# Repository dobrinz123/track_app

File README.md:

# Circuit Timer

An **advisory, recreational** GNSS lap-timing app for the Transilvania Motor Ring (Cerghid, Mureș County, Romania) — not an official timing system, and no substitute for organizer or FIM/FIA timing. It's a React Native / Expo app (iOS-first, Android supported) backed by a pure TypeScript timing/geometry core.

See `docs/decisions/ADR-0001-stack.md` for the stack decision, `docs/decisions/ADR-0003-ios-primary-target.md` for why iOS is the primary target, and `docs/architecture/contracts.md` for the binding module contracts.

## Quickstart (Windows + iPhone, free sideload path)

Expo Go is retired for this app's SDK — there's no more QR-code dev loop. Both
development and on-track use now go through a sideloaded standalone build. See
[`docs/ios-no-mac-workflow.md`](docs/ios-no-mac-workflow.md) for the full,
beginner-proof guide: the GitHub Actions workflow that builds unsigned `.ipa`
artifacts, and installing/re-signing them on Windows with Sideloadly and a free
Apple ID (no paid Apple Developer account required).

```
npm install
```

Then follow [`docs/ios-no-mac-workflow.md`](docs/ios-no-mac-workflow.md) §b onward to
build via CI, sideload to your iPhone, and (§e) run the dev-client build against
`npx expo start` from `apps/mobile` for fast iteration.

## Monorepo layout

npm workspaces (`packages/*`, `apps/*`):

```
packages/core/    @circuit/core — pure TypeScript domain package (geometry, timing,
                  calibration, session-state contracts). Zero React/React
                  Native/Expo imports, enforced by an ESLint no-restricted-imports
                  rule. Vitest + fast-check for unit/property tests, Zod for schema
                  validation.
apps/mobile/      mobile — Expo (TypeScript) app. Imports @circuit/core via
                  the workspace; Metro is configured for monorepo resolution.
```

## Prerequisites

- Node.js 24.x and npm 11.x.
- No Android SDK / Xcode / Flutter required for typecheck, test, lint, or the
  Metro export steps below. Native builds (APK/IPA) additionally require Android
  Studio / Xcode (out of scope on this Windows build machine) or
  [EAS Build](https://docs.expo.dev/build/introduction/), which runs in the cloud
  and needs neither — see `docs/ios-no-mac-workflow.md` for the iOS path.

## Install

```
npm install
```

Installs and links all workspaces from the repo root (do not `npm install` inside
individual packages).

## Verification commands

From the repo root:

```
npm run typecheck   # tsc --noEmit across all workspaces
npm test             # vitest run in packages/core
npm run lint          # eslint . (flat config, applied to both workspaces)
npm run format         # prettier --write .
```

To verify the mobile app bundles correctly with Metro (no Android SDK / Xcode needed —
both platforms are machine-verifiable gates per `docs/decisions/ADR-0003-ios-primary-target.md` §5):

```
cd apps/mobile
npx expo export --platform ios --output-dir dist-export
npx expo export --platform android --output-dir dist-export
```

To run the app itself on an iPhone: a sideloaded dev-client build (see Quickstart above
and `docs/ios-no-mac-workflow.md`), or `npm run ios` / `npm run android` / `npm run web`
from `apps/mobile` with the relevant SDK/simulator installed.

## Docs index

- [`docs/ios-no-mac-workflow.md`](docs/ios-no-mac-workflow.md) — canonical Windows-host,
  iPhone-device workflow: free unsigned-`.ipa` CI builds + Sideloadly (dev-client and
  release, no paid account), offline on-track operation, troubleshooting.
- [`docs/verification/real-track-validation-checklist.md`](docs/verification/real-track-validation-checklist.md) —
  printable physical validation protocol at Transilvania Motor Ring.
- [`docs/verification/baseline.md`](docs/verification/baseline.md) — repository state at project start.
- [`docs/architecture/contracts.md`](docs/architecture/contracts.md) — binding module contracts (canonical interfaces).
- [`docs/architecture/current-state.md`](docs/architecture/current-state.md) — living summary of the target architecture.
- [`docs/implementation-plan.md`](docs/implementation-plan.md) — work-package breakdown and verification strategy.
- [`docs/research/transilvania-motor-ring.md`](docs/research/transilvania-motor-ring.md) — circuit research packet
  (location, length, OSM geometry addendum, known gaps).
- [`docs/decisions/ADR-0001-stack.md`](docs/decisions/ADR-0001-stack.md) — mobile stack: React Native (Expo) + TypeScript monorepo.
- [`docs/decisions/ADR-0002-circuit-geometry-source.md`](docs/decisions/ADR-0002-circuit-geometry-source.md) — circuit geometry
  provenance (OSM-derived centerline, app-defined gates) and license attribution.
- [`docs/decisions/ADR-0003-ios-primary-target.md`](docs/decisions/ADR-0003-ios-primary-target.md) — iOS as the primary
  target platform: Location configuration, Info.plist, monotonic timing, thermal/battery, verification gates.
- [`docs/decisions/ADR-0004-no-mac-ios-workflow.md`](docs/decisions/ADR-0004-no-mac-ios-workflow.md) — iOS without a Mac:
  original Expo Go development + EAS cloud builds decision; dev-loop portion superseded by ADR-0005.
- [`docs/decisions/ADR-0005-free-install-path.md`](docs/decisions/ADR-0005-free-install-path.md) — free iOS install
  path: GitHub Actions unsigned `.ipa` builds + Sideloadly (free Apple ID), replacing the retired Expo Go dev loop.
- [`docs/algorithms/calibration.md`](docs/algorithms/calibration.md) — the Learn-lap calibration engine: quality
  thresholds, coverage bins, direction detection, bounded bias estimation, acceptance criteria, confidence blend.
- [`docs/algorithms/timing-and-crossings.md`](docs/algorithms/timing-and-crossings.md) — directed-gate crossing
  semantics, rearm/debounce, lap/sector validity rules and invalid-reason codes, monotonic-time rules.
- [`docs/algorithms/live-delta.md`](docs/algorithms/live-delta.md) — reference-lap resampling, PB replacement rules,
  live delta computation, EMA smoothing, confidence/staleness handling, sign convention.
- [`docs/persistence-model.md`](docs/persistence-model.md) — SQL table schema (v1/v2), migration approach, checkpoint
  cadence, ADR-0003 §3 recovery flow, `sessionId` convention, `deleteUserData` coverage, retention.
- [`docs/testing-and-replay.md`](docs/testing-and-replay.md) — test architecture (unit/property/contract/integration),
  the fixture catalog, how to run the suites, using `DevReplayScreen` on-device, determinism rules.
- [`docs/known-limitations.md`](docs/known-limitations.md) — an honest list of the app's real constraints and
  implementation gaps.
- [`docs/privacy.md`](docs/privacy.md) — data inventory, permission posture, deletion path, diagnostics content,
  the advisory-tool disclaimer.
- [`docs/adding-a-circuit.md`](docs/adding-a-circuit.md) — onboarding a future circuit: profile schema, provenance
  rules, the generator-script pattern, validation gates, `layoutVersion` discipline.

## License / attribution

Circuit centerline and pit-lane geometry are derived from OpenStreetMap (way `488429454` and way `488429716`),
© OpenStreetMap contributors, licensed under the **Open Database License (ODbL) 1.0**. Start/finish and sector
gates are **app-defined**, not official — see `docs/decisions/ADR-0002-circuit-geometry-source.md` for full
provenance and the attribution requirement.

## Known limitations

- Native binaries are not built or verified on this machine; only the Metro
  (JS bundle) export is machine-verifiable here, per `docs/decisions/ADR-0001-stack.md`.
  Native builds (APK/IPA) run via EAS Build in the cloud.
- Circuit geometry is community-derived (OpenStreetMap), and start/finish/sector gates
  are app-defined, not sourced from official circuit or FIM/FIA documentation — see
  `docs/decisions/ADR-0002-circuit-geometry-source.md`. Physical on-track validation
  (`docs/verification/real-track-validation-checklist.md`) is the reference check against
  this gap.

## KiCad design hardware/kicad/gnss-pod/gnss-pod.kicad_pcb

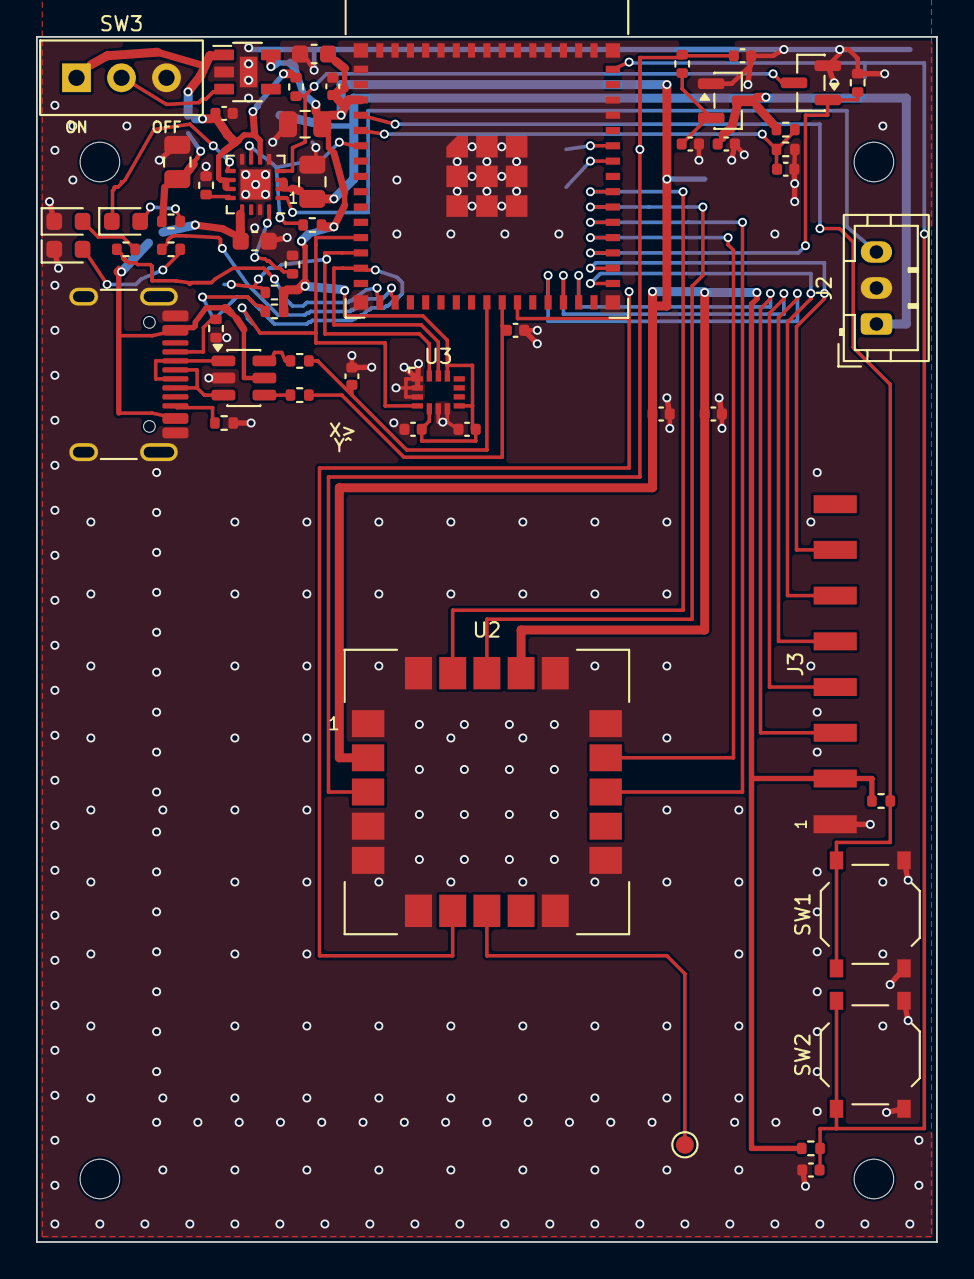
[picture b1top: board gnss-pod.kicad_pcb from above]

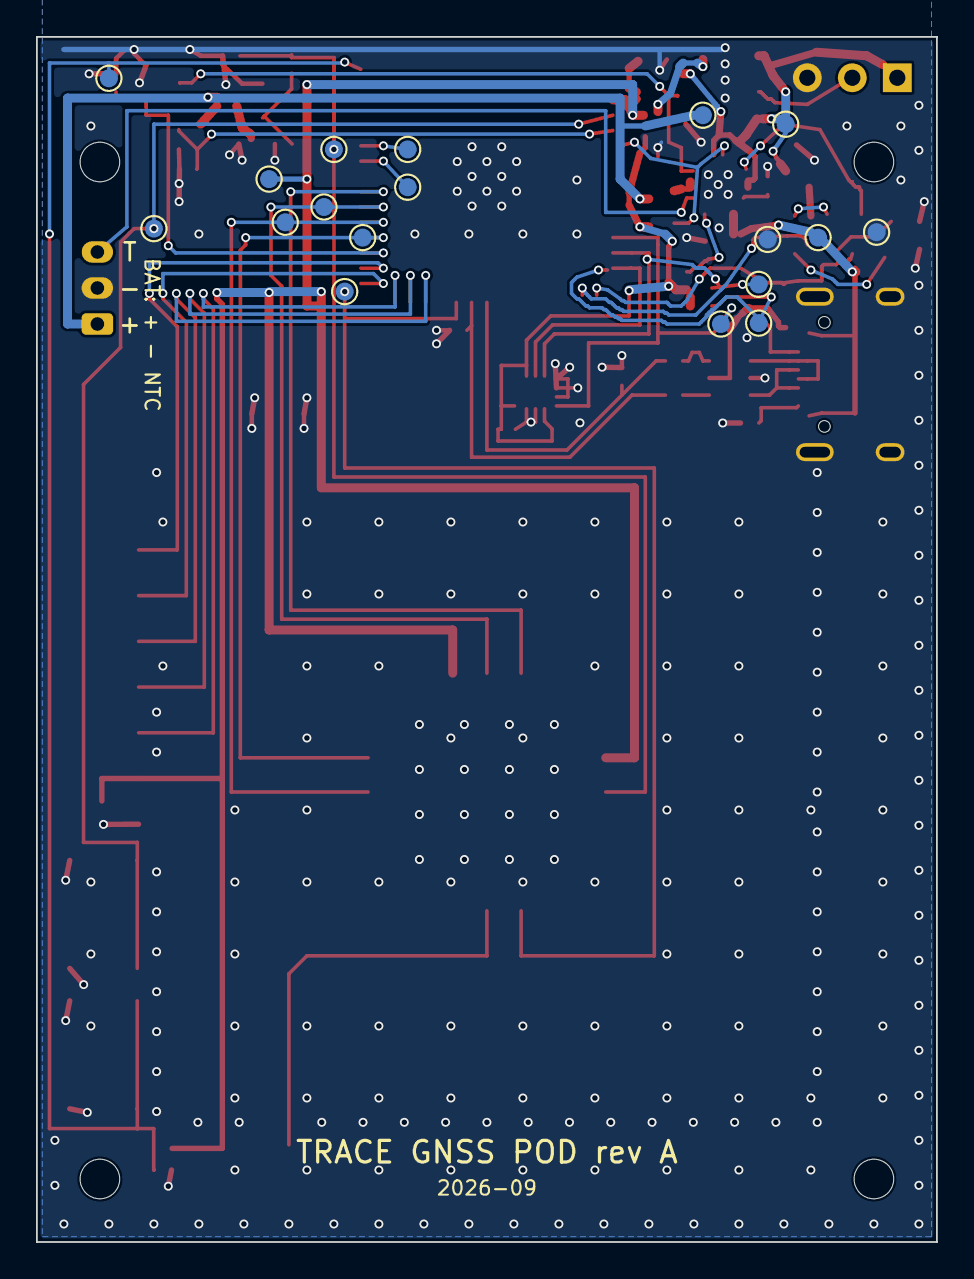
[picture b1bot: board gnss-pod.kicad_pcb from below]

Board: 2 copper layers, 50.0 x 67.0 mm, 77 parts (18 on the bottom side), 45 nets.

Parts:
C1: 1uF 50V X5R 0603; C_0603_1608Metric
C2, C3, C6: 22uF 25V X5R 0805; C_0805_2012Metric
C4, C8, C12, C13: 1uF 25V X5R 0402; C_0402_1005Metric
C5: 10uF 10V X5R 0603; C_0603_1608Metric
C7, C10, C11, C14, C15, C16: 100nF 16V X7R 0402; C_0402_1005Metric
C9: 4.7uF 10V X5R 0402; C_0402_1005Metric
C17, C18: DNP; C_0402_1005Metric
J1: TYPE-C-31-M-12; USB_C_Receptacle_HRO_TYPE-C-31-M-12
J2: B3B-PH-K-S(LF)(SN); JST_PH_B3B-PH-K_1x03_P2.00mm_Vertical
J3: DNP 1x8 spare pads; PadRow_1x08_P2.54mm_SMD
LED1: KT-0603Y yellow; LED_0603_1608Metric
LED2: KT-0603R red; LED_0603_1608Metric
LED3: KT-0603R red CHG; LED_0603_1608Metric
MH1, MH2, MH3, MH4: M2; MountingHole_2.2mm_M2
Q1: 2N7002; SOT-23
R1, R2: 5.1k 1%; R_0402_1005Metric
R3, R4: 22R; R_0402_1005Metric
R5, R6, R19: 10k 1%; R_0402_1005Metric
R7, R8: 4.7k 1%; R_0402_1005Metric
R9: 3.3k 1%; R_0402_1005Metric
R10, R11: 1.5k 1%; R_0402_1005Metric
R12, R18: 100k 1%; R_0402_1005Metric
R13, R14: 1M 1%; R_0402_1005Metric
R15, R16: 1k 1%; R_0402_1005Metric
R17: 0R; R_0402_1005Metric
SW1: TS-1187A-B-A-B BOOT; SW_Push_1P1T_XKB_TS-1187A
SW2: TS-1187A-B-A-B RESET; SW_Push_1P1T_XKB_TS-1187A
SW3: SS-12D00-G3 POWER; SW_Slide_SPDT_SOFNG_SS-12D00-G3
TP1, TP2, TP3, TP4, TP5, TP6, TP7, TP8, TP9, TP10, TP11, TP12, TP13, TP14, TP15, TP16, TP17, TP18, TP19: TP; TestPoint_Pad_D1.0mm
U1: ESP32-S3-MINI-1-N8; ESP32-S3-MINI-1
U2: SAM-M10Q-00B; u-blox_SAM-M10Q
U3: LSM6DSV16XTR; LGA-14_2.5x3mm_P0.5mm_LSM6DSV16X
U4: BQ24073RGTR; TI_RGT0016C_VQFN-16_3x3mm_P0.5mm_EP1.68mm
U5: TLV75733PDYDR; TI_DYD0005A_SOT-23-5_ThermalPad
U6: XC6206P332MR-G; SOT-23
U7: USBLC6-2SC6; SOT-23-6_USBLC6-2_FlowThrough

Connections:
3V3: C5.1, C6.1, C7.1, C9.1, C10.1, C14.1, C15.1, J3.2, R5.2, R6.2, R7.2, R8.2, R12.2, TP1.1, U1.3, U2.2, U2.17, U3.5, U3.8, U3.12, U5.5
BOOT: R6.1, SW1.1, TP17.1, U1.4
CC1: J1.A5, R1.1
CC2: J1.B5, R2.1
CHG_CE: Q1.3, R18.1, U4.4
CHG_EN: Q1.1, R19.1, U1.33
CHG_N: LED3.1, U4.9
EN: C8.1, R5.1, SW2.1, TP16.1, U1.45
GND: C1.2, C2.2, C3.2, C4.2, C5.2, C6.2, C7.2, C8.2, C9.2, C10.2, C11.2, C12.2, C13.2, C14.2, C15.2, C16.2, C17.2, C18.2, J1.A1, J1.A12, J1.B1, J1.B12, J1.SH, J2.2, J3.1, LED1.1, LED2.1, Q1.2, R1.2, R2.2, R9.2, R10.2, R14.2, R19.2, SW1.2, SW2.2, SW3.3, TP2.1, TP3.1, U1.1, U1.2, U1.42, U1.43, U1.46, U1.47, U1.48, U1.49, U1.50, U1.51, U1.52, U1.53, U1.54, U1.55, U1.56, U1.57, U1.58, U1.59, U1.60, U1.61, U1.62, U1.63, U1.64, U1.65, U2.1, U2.4, U2.5, U2.6, U2.10, U2.11, U2.15, U2.16, U2.20, U3.1, U3.2, U3.3, U3.6, U3.7, U4.5, U4.8, U4.15, U4.17, U5.2, U5.6, U6.1, U7.2
GNSS_EXTINT: U1.37, U2.19
GNSS_RESET_N: TP15.1, U1.36, U2.18
GNSS_RXD: TP8.1, U1.34, U2.14
GNSS_SAFEBOOT_N: TP12.1, U2.8
GNSS_TXD: TP7.1, U1.35, U2.13
I2C_SCL: R8.1, TP11.1, U1.14, U3.13
I2C_SDA: R7.1, TP10.1, U1.13, U3.14
ILIM: R10.1, U4.12
IMU_INT1: TP19.1, U1.12, U3.4
IO33: J3.4, U1.28
IO34: J3.3, U1.29
IO35: J3.6, U1.31
IO36: J3.7, U1.32
IO47: J3.5, U1.27
ISET: R9.1, U4.16
LDO_EN: SW3.2, U5.3
LED1: R15.1, U1.16
LED1_A: LED1.2, R15.2
LED2: R16.1, U1.17
LED2_A: LED2.2, R16.2
LED3_A: LED3.2, R11.2
PGOOD_N: R12.1, U1.6, U4.7
PPS: TP9.1, U1.25, U2.7
TS: J2.3, U4.1
U0RXD: TP14.1, U1.40
U0TXD: TP13.1, U1.39
USB_DN: C18.1, R4.2, U1.23
USB_DN_C: J1.A7, J1.B7, R4.1, U7.1, U7.6
USB_DP: C17.1, R3.2, U1.24
USB_DP_C: J1.A6, J1.B6, R3.1, U7.3, U7.4
VBAT: C3.1, C12.1, J2.1, R13.1, TP4.1, U4.2, U4.3, U6.3
VBAT_SENSE: C16.1, R13.2, R14.1, U1.5
VBCKP: C11.1, R17.2, TP18.1, U2.3
VBCKP_SRC: C13.1, R17.1, U6.2
VBUS: C1.1, J1.A4, J1.A9, J1.B4, J1.B9, TP6.1, U4.13, U7.5
VSYS: C2.1, C4.1, R11.1, R18.2, SW3.1, TP5.1, U4.6, U4.10, U4.11, U5.1

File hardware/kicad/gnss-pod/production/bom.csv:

Comment,Designator,Footprint,LCSC
1uF 50V X5R 0603,C1,C_0603_1608Metric,C15849
100nF 16V X7R 0402,"C7,C10,C11,C14,C15,C16",C_0402_1005Metric,C1525
1uF 25V X5R 0402,"C4,C8,C12,C13",C_0402_1005Metric,C52923
22uF 25V X5R 0805,"C2,C3,C6",C_0805_2012Metric,C45783
10uF 10V X5R 0603,C5,C_0603_1608Metric,C19702
4.7uF 10V X5R 0402,C9,C_0402_1005Metric,C23733
TYPE-C-31-M-12 (JLCPCB SMT; 4 shell tabs are plated slots (THT) - JLCPCB to hand/THT-solder or owner solders them (spec sec 9 item 3)),J1,USB_C_Receptacle_HRO_TYPE-C-31-M-12,C165948
"B3B-PH-K-S(LF)(SN) (DO NOT FIT ON REV A - USB-only units (owner decision 2026-09-24, spec sec 2))",J2,JST_PH_B3B-PH-K_1x03_P2.00mm_Vertical,C131339
KT-0603Y yellow,LED1,LED_0603_1608Metric,C2287
KT-0603R red,LED2,LED_0603_1608Metric,C2286
KT-0603R red CHG,LED3,LED_0603_1608Metric,C2286
2N7002,Q1,SOT-23,C8545
5.1k 1%,"R1,R2",R_0402_1005Metric,C25905
1.5k 1%,"R10,R11",R_0402_1005Metric,C25867
100k 1%,"R12,R18",R_0402_1005Metric,C25741
1M 1%,"R13,R14",R_0402_1005Metric,C26083
1k 1%,"R15,R16",R_0402_1005Metric,C11702
0R,R17,R_0402_1005Metric,C17168
10k 1%,"R5,R6,R19",R_0402_1005Metric,C25744
22R,"R3,R4",R_0402_1005Metric,C25092
4.7k 1%,"R7,R8",R_0402_1005Metric,C25900
3.3k 1%,R9,R_0402_1005Metric,C25890
TS-1187A-B-A-B BOOT,SW1,SW_Push_1P1T_XKB_TS-1187A,C318884
TS-1187A-B-A-B RESET,SW2,SW_Push_1P1T_XKB_TS-1187A,C318884
"SS-12D00-G3 POWER (HAND-SOLDER by owner - NOT in CPL (bought loose, spec sec 9))",SW3,SW_Slide_SPDT_SOFNG_SS-12D00-G3,C22355741
ESP32-S3-MINI-1-N8,U1,ESP32-S3-MINI-1,C2913206
SAM-M10Q-00B,U2,u-blox_SAM-M10Q,C5443880
LSM6DSV16XTR,U3,LGA-14_2.5x3mm_P0.5mm_LSM6DSV16X,C5267406
BQ24073RGTR,U4,TI_RGT0016C_VQFN-16_3x3mm_P0.5mm_EP1.68mm,C15220
TLV75733PDYDR,U5,TI_DYD0005A_SOT-23-5_ThermalPad,C22399950
XC6206P332MR-G,U6,SOT-23,C5446
USBLC6-2SC6,U7,SOT-23-6_USBLC6-2_FlowThrough,C7519

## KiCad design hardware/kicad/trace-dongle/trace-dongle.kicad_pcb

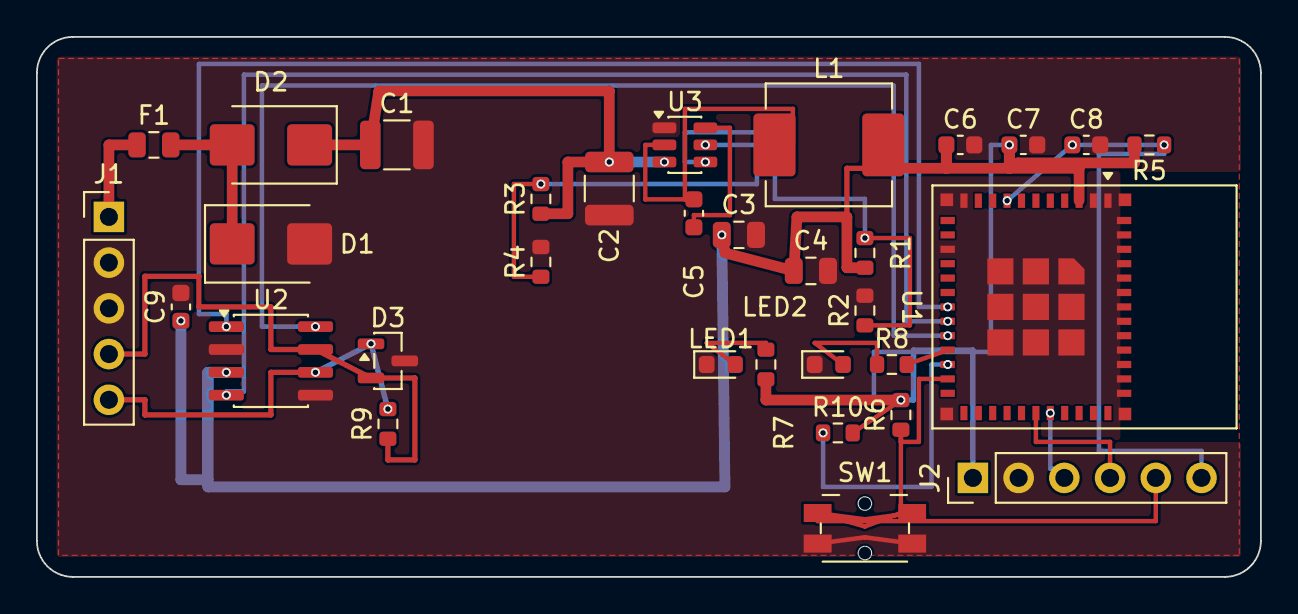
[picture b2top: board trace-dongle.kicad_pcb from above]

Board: 2 copper layers, 68.0 x 30.0 mm, 32 parts (0 on the bottom side), 22 nets.

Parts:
C1, C2: 10uF/50V X7R 1210; C_1210_3225Metric
C3, C4: 22uF/10V X7R 0805; C_0805_2012Metric
C5: 100nF (BST); C_0603_1608Metric
C6: 100nF (U1 3V3); C_0603_1608Metric
C7: 10uF (U1 3V3); C_0603_1608Metric
C8: 1uF (U1 EN); C_0603_1608Metric
C9: 100nF (U2 VCC); C_0603_1608Metric
D1: SMBJ18A; D_SMB
D2: SS34B; D_SMB
D3: PESD2CANFD24V-TR; SOT-23
F1: PTC 350mA 24V; Fuse_0805_2012Metric
J1: OBD-II 5-pad fallback row (12V/GND/GND/CANH/CANL)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; PinHeader_1x05_P2.54mm_Vertical
J2: 1x6 2.54mm UART header -- hand-solder, HTSW-106-0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; PinHeader_1x06_P2.54mm_Vertical
L1: 10uH 2A shielded; L_APV_APH0630
LED1: green (power); LED_0603_1608Metric
LED2: amber/orange (activity); LED_0603_1608Metric
R1: 100k (FB div hi); R_0603_1608Metric
R2: 22.1k (FB div lo); R_0603_1608Metric
R3: 274k (EN div hi); R_0603_1608Metric
R4: 44.2k (EN div lo); R_0603_1608Metric
R5: 10k (U1 EN pullup); R_0603_1608Metric
R6: 10k (IO9/BOOT pullup); R_0603_1608Metric
R7, R8: 1k; R_0603_1608Metric
R9: DNP (CAN term, not fitted); R_0603_1608Metric
R10: 10k (IO8 pullup, boot-mode high); R_0603_1608Metric
SW1: BOOT tact; Panasonic_EVQPUL_EVQPUC
U1: ESP32-C3-MINI-1-N4; ESP32-C3-MINI-1
U2: TCAN330DR; SOIC-8_3.9x4.9mm_P1.27mm
U3: TPS54202DDCR; SOT-23-6

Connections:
3V3: C3.1, C4.1, C6.1, C7.1, C9.1, J2.1, L1.2, R1.1, R5.2, R6.2, R7.1, R10.2, U1.3, U2.3
12V_RAW: F1.1, J1.1
BST_NODE: C5.1, U3.6
CANH: D3.2, J1.4, R9.1, U2.7
CANL: D3.1, J1.5, R9.2, U2.6
CAN_RX: U1.19, U2.4
CAN_S: U1.20, U2.8
CAN_TX: U1.18, U2.1
EN_U3_NODE: R3.2, R4.1, U3.5
FB_NODE: R1.2, R2.1, U3.4
GND: C1.2, C2.2, C3.2, C4.2, C6.2, C7.2, C8.2, C9.2, D1.2, D3.3, J1.2, J1.3, J2.2, LED1.1, LED2.1, R2.2, R4.2, SW1.2, U1.1, U1.2, U1.11, U1.14, U1.36, U1.37, U1.38, U1.39, U1.40, U1.41, U1.42, U1.43, U1.44, U1.45, U1.46, U1.47, U1.48, U1.49, U1.50, U1.51, U1.52, U1.53, U2.2, U2.5, U3.1
IO8_PU: R10.1, U1.22
IO9_BOOT: J2.5, R6.1, SW1.1, U1.23
LED1_TOP: LED1.2, R7.2
LED2_DRIVE: R8.2, U1.21
LED2_TOP: LED2.2, R8.1
NET_FUSED: D1.1, D2.2, F1.2
RXD0: J2.4, U1.30
SW_NODE: C5.2, L1.1, U3.2
TXD0: J2.3, U1.31
U1_EN: C8.1, J2.6, R5.1, U1.8
VIN_PROT: C1.1, C2.1, D2.1, R3.1, U3.3

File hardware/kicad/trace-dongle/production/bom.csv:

Comment,Designator,Footprint,LCSC
10uF/50V X7R 1210,C1,C_1210_3225Metric,C138687
10uF/50V X7R 1210,C2,C_1210_3225Metric,C138687
22uF/10V X7R 0805,C3,C_0805_2012Metric,C907991
22uF/10V X7R 0805,C4,C_0805_2012Metric,C907991
100nF (BST),C5,C_0603_1608Metric,C1591
100nF (U1 3V3),C6,C_0603_1608Metric,C1591
10uF (U1 3V3),C7,C_0603_1608Metric,C96446
1uF (U1 EN),C8,C_0603_1608Metric,C5673
100nF (U2 VCC),C9,C_0603_1608Metric,C1591
SMBJ18A,D1,D_SMB,C151256
SS34B,D2,D_SMB,C880746
PESD2CANFD24V-TR,D3,SOT-23,C552486
PTC 350mA 24V,F1,Fuse_0805_2012Metric,C910821
"OBD-II 5-pad fallback row (12V/GND/GND/CANH/CANL) -- hand-solder, TSW-105-07-T-S 1x5 header",J1,PinHeader_1x05_P2.54mm_Vertical,C5967238
"1x6 2.54mm UART header -- hand-solder, HTSW-106-07-T-S 1x6 header",J2,PinHeader_1x06_P2.54mm_Vertical,C6209271
10uH 2A shielded,L1,L_APV_APH0630,C167223
green (power),LED1,LED_0603_1608Metric,C84267
amber/orange (activity),LED2,LED_0603_1608Metric,C84269
100k (FB div hi),R1,R_0603_1608Metric,C25803
"10k (IO8 pullup, boot-mode high)",R10,R_0603_1608Metric,C2906982
22.1k (FB div lo),R2,R_0603_1608Metric,C25961
274k (EN div hi),R3,R_0603_1608Metric,C22968
44.2k (EN div lo),R4,R_0603_1608Metric,C23056
10k (U1 EN pullup),R5,R_0603_1608Metric,C2906982
10k (IO9/BOOT pullup),R6,R_0603_1608Metric,C2906982
1k,R7,R_0603_1608Metric,C2907002
1k,R8,R_0603_1608Metric,C2907002
BOOT tact,SW1,Panasonic_EVQPUL_EVQPUC,C79174
ESP32-C3-MINI-1-N4,U1,ESP32-C3-MINI-1,C2838502
TCAN330DR,U2,SOIC-8_3.9x4.9mm_P1.27mm,C2652876
TPS54202DDCR,U3,SOT-23-6,C191884

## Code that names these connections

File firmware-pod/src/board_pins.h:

#ifndef TRACE_POD_BOARD_PINS_H
#define TRACE_POD_BOARD_PINS_H

/*
 * TRACE GNSS Pod rev A pin map. Every number below is from
 * hardware/gnss-pod/DESIGN-REV-A.md §4 (netlist) and §6 (GPIO assignment and
 * binding firmware rules). Change nothing here without changing the design.
 */

/* §6: "Never configure GPIO21 as an output." SAM-M10Q TIMEPULSE, which is
 * internally tied to SAFEBOOT_N through 1 kΩ: driving it low at GNSS
 * power-up would put the receiver into safeboot. INPUT ONLY, no pulls. */
#define PIN_PPS 21

/* §6: UART1 on GPIO38 (MCU TX -> GNSS RXD) / GPIO39 (GNSS TXD -> MCU RX). */
#define PIN_GNSS_UART_TX 38
#define PIN_GNSS_UART_RX 39

/* §6: "Drive GPIO40 only as open-drain low for >= 1 ms to reset the GNSS,
 * and remember that reset clears BBR." */
#define PIN_GNSS_RESET_N 40
/* GNSS EXTINT: output-capable, unused on rev A (OBD time-marking is phase 2).
 * Left untouched (reset state = input); the GNSS pull-up keeps it inactive. */
#define PIN_GNSS_EXTINT 41

/* §6 (review fix wave): IMU I2C on GPIO9 (SDA) / GPIO10 (SCL), INT1 on
 * GPIO8; INT2 is NOT connected, so every interrupt source goes to INT1. */
#define PIN_I2C_SDA 9
#define PIN_I2C_SCL 10
#define PIN_IMU_INT1 8
#define I2C_FREQ_HZ 400000 /* 400 kHz Fast-mode, R7/R8 4.7 kΩ pull-ups (§3) */

/* §6 (binding, review rev3): GPIO37 = CHG_EN -> Q1 gate. Rev A: LOW AT ALL
 * TIMES (no cell, charging never enabled). R19 holds it low when undriven. */
#define PIN_CHG_EN 37

/* §4: PGOOD_N from the BQ24073 (open-drain, R12 100 kΩ to 3V3).
 * LOW = valid USB input present. */
#define PIN_PGOOD_N 2

/* §2 / §6: VBAT_SENSE on GPIO1 = ADC1_CH0, 1 MΩ/1 MΩ divider; ADC1 only,
 * ATTEN3 (11 dB, 0-2900 mV). On rev A (J2 not fitted) it reads ~0 V. */
#define PIN_VBAT_SENSE 1

/* §3 / §4: LED1 yellow on GPIO12, LED2 red on GPIO13 (active high, 1 kΩ). */
#define PIN_LED_YELLOW 12
#define PIN_LED_RED 13

/* §4: SW1 BOOT on GPIO0 (strap, R6 10 kΩ pull-up, button to GND). Read as a
 * plain input only after boot; never driven, never given a capacitor-like
 * load (§4 "no capacitor on IO0"). Holding it during reset/power-up selects
 * the ROM download mode, which is its intended strap use. */
#define PIN_BOOT_BUTTON 0

/* Strapping pins GPIO3 / GPIO45 / GPIO46 are NC and never touched (§6). */

#endif /* TRACE_POD_BOARD_PINS_H */

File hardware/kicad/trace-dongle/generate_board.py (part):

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  - U2 CAN transceiver REPLACED: TJA1051T/3 (needs 4.5-5.5V VCC; this
    design has only one 3.3V rail) -> TCAN330DR. Pin map verified against
    the live TI datasheet: 1=TXD, 2=GND, 3=VCC, 4=RXD, 5=SHDN, 6=CANL,
    7=CANH, 8=S -- note pins 5/8 are SWAPPED from what the remediation
    ticket proposed (it said 5=S,8=SHDN); the ticket's map was itself an
    unverified from-memory guess and was wrong. SHDN(5)->GND (device
    stays enabled), S(8)->IO6 (unchanged firmware hw listen-only control
    -- TCAN330DR's S pin is functionally identical to TJA1051T/3's).
    Pins 1/2/3/4/6/7 (TXD/GND/VCC/RXD/CANL/CANH) are numerically IDENTICAL
    between the two parts, so only pin 5's net membership changes
    (3V3->GND) and the old VCC<->VIO jumper route is removed (would now
    short VCC to GND).
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    against the same convention already confirmed for D_SMB/PESD2CANFD);
    the board had pad 1 wired to the series resistor and pad 2 to GND,
    reversed, which would leave both LEDs dark.
  - LED2 moved off strapping pin IO8 -> IO7 (non-strapping); IO8 now
    carries only a new 10k pullup (R10) to guarantee a HIGH boot-mode
    level for J2 UART flashing.
  - C1/C2 (buck input caps): 22uF/35V in 0603 was never a real part.
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    # this node.
    "NET_FUSED": [("F1", "2"), ("D2", "2"), ("D1", "1")],
    # D2 pad 1 = cathode after the 180deg rotation, now correctly facing
    # VIN_PROT. U3 pin 3 = VIN (verified TI datasheet; sec7's pin 5 was
    # wrong too).
    "VIN_PROT":  [("D2", "1"), ("C1", "1"), ("C2", "1"), ("R3", "1"), ("U3", "3")],
    # rev A3 item 4: U2 pin 5 (was TJA1051T/3's VIO, now TCAN330DR's SHDN)
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    "U1_EN":     [("U1", "8"), ("R5", "1"), ("C8", "1"), ("J2", "6")],
    "IO9_BOOT":  [("U1", "23"), ("R6", "1"), ("SW1", "1"), ("J2", "5")],
    # U2 pin map verified against the live TI TCAN330 datasheet (SOIC-8):
    # 1=TXD, 2=GND, 3=VCC, 4=RXD, 5=SHDN, 6=CANL, 7=CANH, 8=S. Pins
    # 1/4/6/7/8 are numerically identical to TJA1051T/3's map, so CAN_TX/
    # RX/S/CANH/CANL below are unchanged from wave 2.
    "CAN_TX":    [("U1", "18"), ("U2", "1")],
    "CAN_RX":    [("U1", "19"), ("U2", "4")],
    "CAN_S":     [("U1", "20"), ("U2", "8")],
    # rev A3 item 7: LED2 moved off strapping pin IO8 (22) -> IO7 (21).
    "LED2_DRIVE": [("U1", "21"), ("R8", "2")],
    # NEW (item 7): IO8 (22) now carries only R10's pullup.
    "IO8_PU":    [("U1", "22"), ("R10", "1")],
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    # (also otherwise-isolated 3V3, see below), sharing one bridge to C6.1.
    ("3V3", "R7", "1", "R6", "2", W_POWER, "W", [(35.5 + REV_A3_SHIFT, 20.175), (43.0 + REV_A3_SHIFT, 20.175)]),

    # rev A3 item 7: LED2 driven from IO7 (pin 21) now, not IO8 (pin 22) --
    # same short direct F.Cu hop pattern the old IO8 drive used (IO7 is
    # 0.8mm north of IO8 in the same physical pin column).
    ("LED2_DRIVE", "U1", "21", "R8", "2", W_SIGNAL, "F", None),
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
    # NEW (rev A3 item 7): IO8 (pin 22) -> R10.1 (verified pad position
    # 43.675,22.0) pullup. IO8 sits in the same physical pin column as
    # IO9 (pin 23, see the IO9_BOOT route below) -- step off in X
    # immediately at IO8's own Y before descending, same pattern but a
    # SHORT step (to 49.7, not IO9_BOOT's 49.0) that clears both the pin
    # column itself and LED2_DRIVE's diagonal (which only reaches this Y
    # band right at R8's pad, x=47.9 -- 0.5mm+ west of this dodge) while
    # staying 0.7mm east of IO9_BOOT's own dodge column. B.Cu throughout
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    ("3V3", "J2", "1", "R6", "2", W_POWER_THIN, "BW",
     [(52.0, 17.4), (48.7, 17.4), (48.7, 20.175)]),

    # -- U1_EN, B.Cu throughout. U1's row-1-11 pins are on a strict 0.8mm
    #    pitch with 0.8mm-wide pads -- edge-to-edge with ZERO gap between
    #    neighbours, so no F.Cu track can thread between any two of them.
    #    Since U1's pads are SMD (F.Cu only), B.Cu passes underneath the
    #    whole row freely. --
    ("U1_EN", "U1", "8", "C8", "1", W_SIGNAL, "B", None),
    # R5.1 (U1_EN) sits east of U1's own pin-36-48 column (R5 rotated
    # 180deg for this).
    ("U1_EN", "C8", "1", "R5", "1", W_SIGNAL, "B", None),
    # R5.1 -> J2.6: B.Cu bridge. rev A4: the enlarged antenna keepout (see
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
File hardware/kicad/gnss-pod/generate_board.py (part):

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    declared as jumpers (internal short), so one pad of each pair carries
    the route. VERIFIED.
  * SW3 SOFNG SS-12D00-G3: the circuit diagram in the drawing shows the
    middle terminal as the common. LDO_EN goes to pin 2 (middle). VERIFIED.
    SPEC ERROR: the pin pitch is 2.5 mm, not 3 mm (G3 = handle length).
  * SAM-M10Q bypass (C9/C10 values): Fig. 28 of the IM was not re-extracted
    here. The values stay as the spec chose them. NOT VERIFIED (schematic).
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#   The cyclic pin order fixes the bundle order, west -> east:
#   PPS 32.9 | V_BCKP 33.5 | V_IO 34.2 | EXTINT 35.9, RESET_N 36.4, VCC 37.1,
#   RXD 38.7, TXD 39.2, SAFEBOOT_N 39.7.
#   PPS, V_BCKP and V_IO leave the west/south pins, go round the west flank
#   and east along the band; PPS then runs west along U1's bottom row into
#   U1.25 (no via at all), V_BCKP climbs past U1 to R17/C11 (no via), V_IO
#   ends on the 3V3 trunk. The north pins go north then east, the east pins
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    ("F_CE", "CHG_CE", 0.2, 1, [(15.4, 7.8), (16.1, 7.1), (40.9, 7.1)]),
    ("F_CE", "CHG_CE", 0.2, 0, [(40.9, 7.1), (41.4, 7.6), (42.06, 7.6)]),        # -> Q1.3 drain
    # V_BCKP: R17.2 -> C11.1 along the north edge (R17 stands vertical so
    # VBCKP_SRC reaches R17.1 from the south; the bottom there is the GND spine)
    ("VBCKP", "VBCKP", 0.2, 0, [(35.85, 6.1), (38.72, 6.1)]),
    ("F_CHGEN", "CHG_EN", 0.2, 0, [(42.7, 16.65), (42.7, 9.4), (43.93, 9.4), (43.93, 8.55)]),
    ("F_CHGEN", "CHG_EN", 0.2, 0, [(43.93, 8.55), (45.6, 8.55), (45.6, 8.11)]),
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    (0.25, 0, [(38.06, 26.0), (38.06, 26.8)]),                                       # C9.2
    (0.25, 0, [(10.36, 24.0), (9.55, 24.0)]),                                        # U7.2 (between D+/D-)
    # review rev2: the bottom under U1's north edge is all W-E lines (EN, CHG_CE,
    # 3V3, VBAT, TS, BOOT, VBAT_SENSE), so the NE top pockets get a GND spine
    # on the bottom along the north edge (from U5's thermal vias) plus drops
    (0.3, 1, [(11.7, 5.65), (11.95, 5.75), (48.5, 5.75)]),                          # spine
    (0.25, 1, [(15.4, 6.9), (15.4, 5.75)]),                                          # C5/C7 drop
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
